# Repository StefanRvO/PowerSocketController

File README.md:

# PowerSocketController
Software for controlling power sockets

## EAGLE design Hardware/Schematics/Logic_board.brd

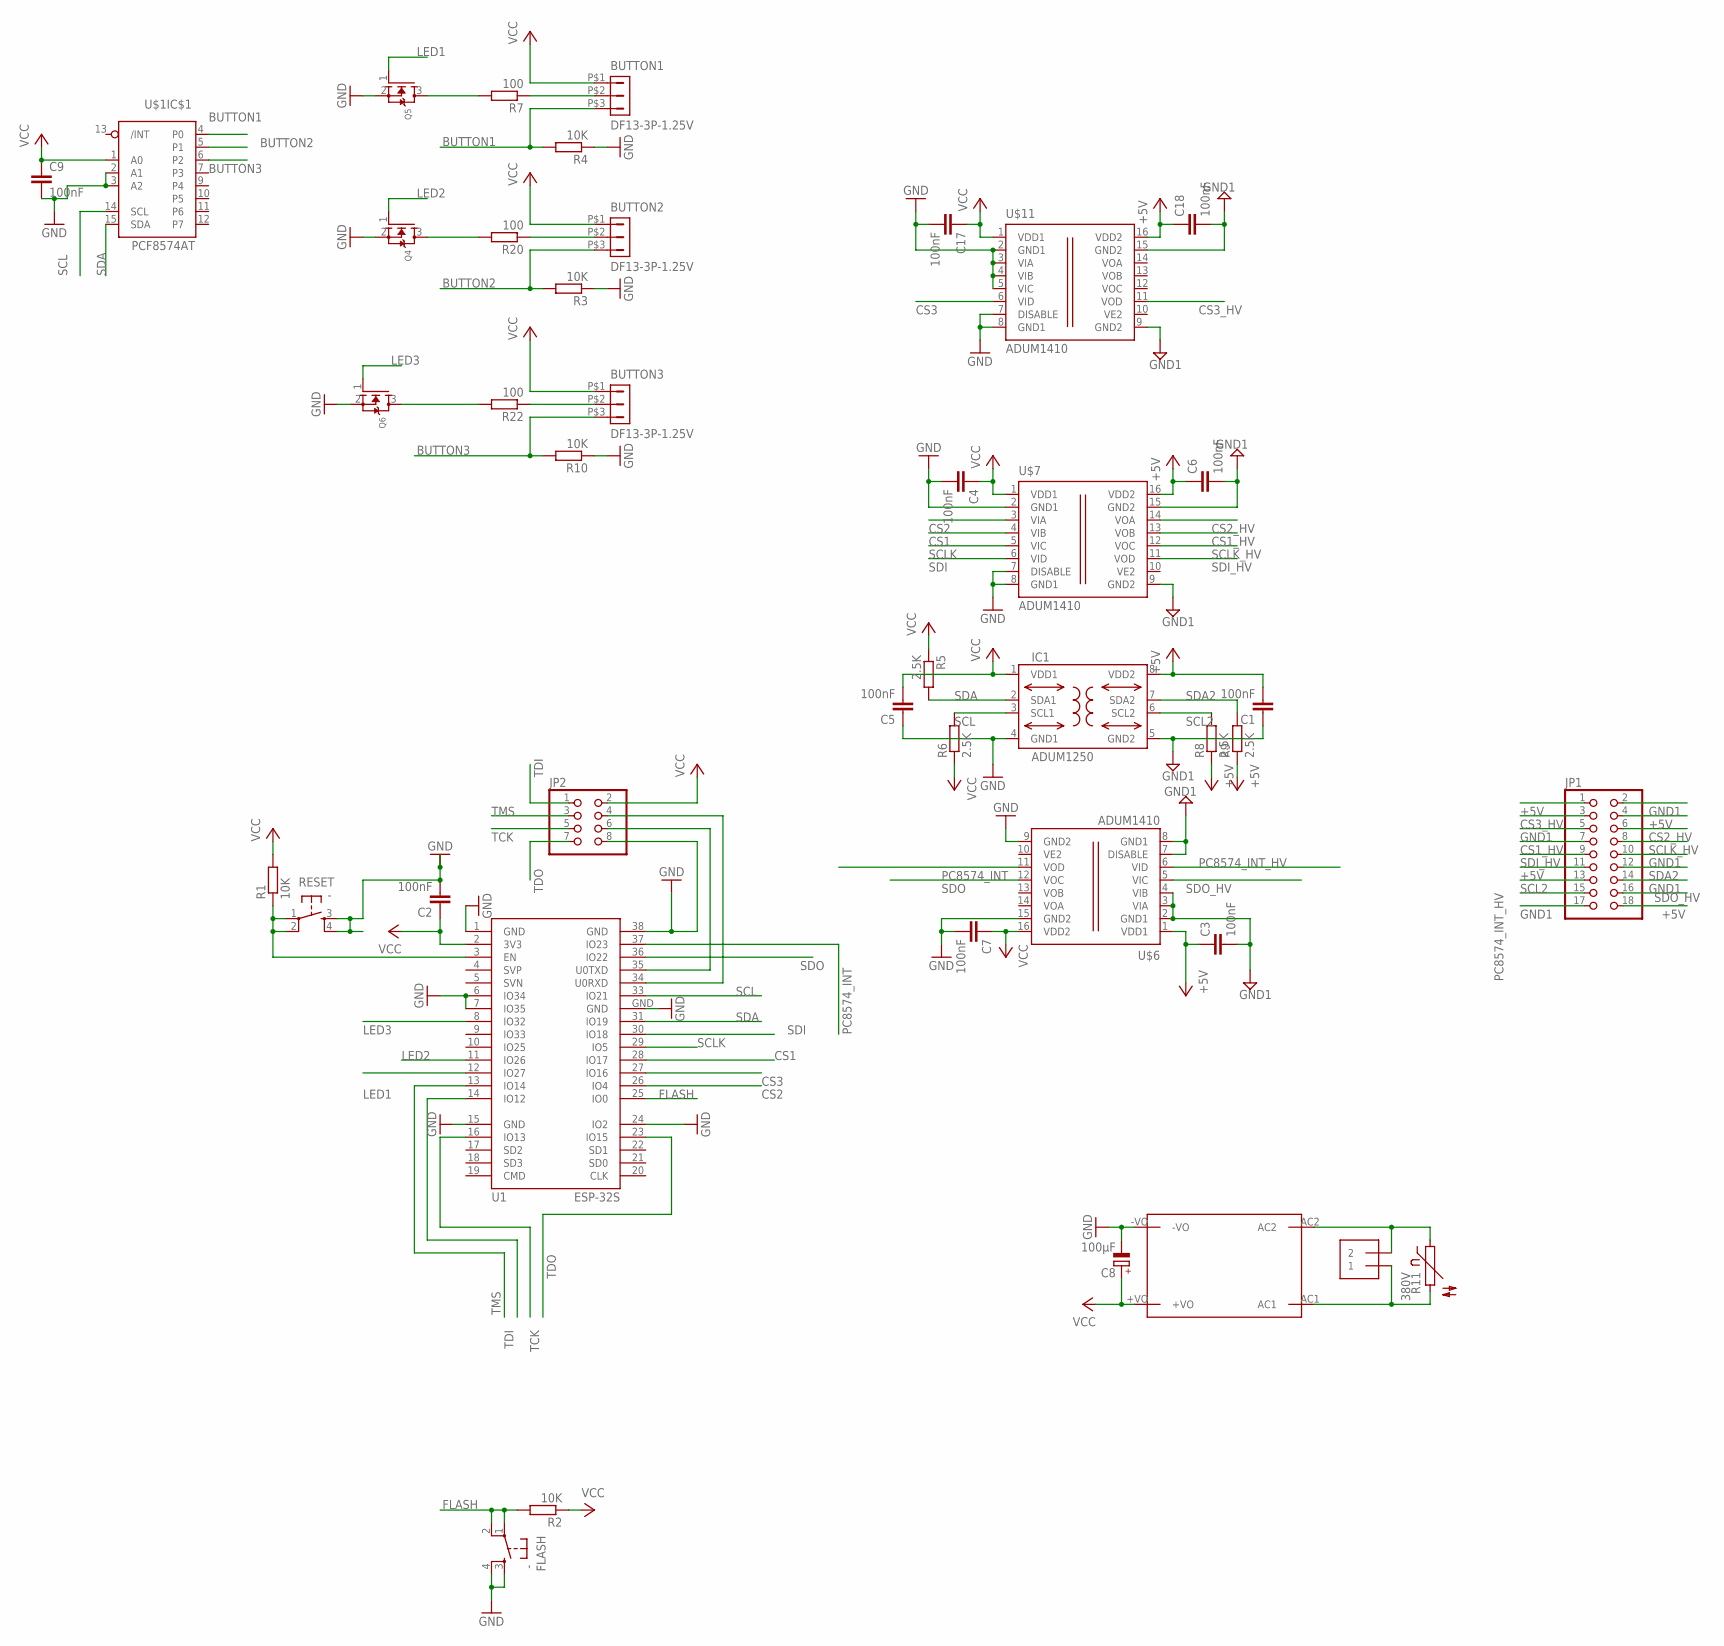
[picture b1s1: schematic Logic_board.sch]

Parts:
BUTTON1, BUTTON2, BUTTON3: DF13-3P-1.25V; DF13C-3P-1.25V
C1, C2, C3, C4, C5, C6, C7, C9, C17, C18: 100nF; C0805
C8: 100µF; E2,5-6
FLASH: -; DTSM-6
IC1: ADUM1250; SO8-COOL
J1: 1X2-3.5MM
JP1: PINHD-2X9; 2X09
JP2: PINHD-2X4; 2X04
Q4, Q5, Q6: MOSFET-NREFLOW; SOT23
R1, R2, R3, R4, R10: 10K; R0805
R5, R6, R8, R9: 2.5K; R0805
R7, R20, R22: 100; R0805
R11: 380V; S14K11
RESET: -; DTSM-6
SUPPLY: 5V; HLK-PM03
U1: ESP-32S
U$1: PCF8574AT; SO16
U$6, U$7, U$11: ADUM1410; SOIC-16

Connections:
+5V: C1.2, C3.1, C6.1, C18.1, IC1.8 (VDD2), JP1.1, JP1.4, JP1.11, JP1.18, R8.1, R9.1, U$6.1 (VDD1), U$7.16 (VDD2), U$11.16 (VDD2)
AC1: J1.1, R11.2, SUPPLY.AC1
AC2: J1.2, R11.1, SUPPLY.AC2
BUTTON1: BUTTON1.P$3 (3), R4.2, U$1.4 (P0)
BUTTON2: BUTTON2.P$3 (3), R3.2, U$1.5 (P1)
BUTTON3: BUTTON3.P$3 (3), R10.2, U$1.6 (P2)
CS1: U1.28 (IO17), U$7.4 (VIB)
CS1_HV: JP1.7, U$7.13 (VOB)
CS2: U1.26 (IO4), U$7.3 (VIA)
CS2_HV: JP1.6, U$7.14 (VOA)
CS3: U1.27 (IO16), U$11.6 (VID)
CS3_HV: JP1.3, U$11.11 (VOD)
FLASH: FLASH.1, FLASH.2, R2.2, U1.25 (IO0)
GND: C2.2, C4.2, C5.1, C7.2, C8.-, C9.2, C17.2, FLASH.3, FLASH.4, IC1.4 (GND1), JP2.8, Q4.2 (S), Q5.2 (S), Q6.2 (S), R3.1, R4.1, R10.1, RESET.3, RESET.4, SUPPLY.-VO, U1.1 (GND), U1.6 (IO34), U1.7 (IO35), U1.15 (GND), U1.24 (IO2), U1.38 (GND), U1.GND, U$1.2 (A1), U$1.3 (A2), U$1.8 (GND), U$6.9 (GND2), U$6.15 (GND2), U$7.2 (GND1), U$7.7 (DISABLE), U$7.8 (GND1), U$11.2 (GND1), U$11.3 (VIA), U$11.4 (VIB), U$11.5 (VIC), U$11.7 (DISABLE), U$11.8 (GND1)
GND1: C1.1, C3.2, C6.2, C18.2, IC1.5 (GND2), JP1.2, JP1.5, JP1.10, JP1.14, JP1.17, U$6.2 (GND1), U$6.3 (VIA), U$6.4 (VIB), U$6.7 (DISABLE), U$6.8 (GND1), U$7.9 (GND2), U$7.15 (GND2), U$11.9 (GND2), U$11.15 (GND2)
LED1: Q5.1 (G), U1.12 (IO27)
LED1_SWITCHED: Q5.3 (D), R7.2
LED2: Q4.1 (G), U1.11 (IO26)
LED2_SWITCHED: Q4.3 (D), R20.2
LED3: Q6.1 (G), U1.8 (IO32)
LED3_SWITCHED: Q6.3 (D), R22.2
unnamed: BUTTON2.P$2 (2), R20.1
unnamed: BUTTON1.P$2 (2), R7.1
unnamed: BUTTON3.P$2 (2), R22.1
unnamed: R1.1, RESET.1, RESET.2, U1.3 (EN)
PC8574_INT: U1.37 (IO23), U$6.11 (VOD)
PC8574_INT_HV: JP1.15, U$6.6 (VID)
RX: JP2.4, U1.34 (U0RXD)
SCL: IC1.3 (SCL1), R6.2, U1.33 (IO21), U$1.14 (SCL)
SCL2: IC1.6 (SCL2), JP1.13, R8.2
SCLK: U1.29 (IO5), U$7.5 (VIC)
SCLK_HV: JP1.8, U$7.12 (VOC)
SDA: IC1.2 (SDA1), R5.2, U1.31 (IO19), U$1.15 (SDA)
SDA2: IC1.7 (SDA2), JP1.12, R9.2
SDI: U1.30 (IO18), U$7.6 (VID)
SDI_HV: JP1.9, U$7.11 (VOD)
SDO: U1.36 (IO22), U$6.12 (VOC)
SDO_HV: JP1.16, U$6.5 (VIC)
TCK: JP2.5, U1.16 (IO13)
TDI: JP2.1, U1.14 (IO12)
TDO: JP2.7, U1.23 (IO15)
TMS: JP2.3, U1.13 (IO14)
TX: JP2.6, U1.35 (U0TXD)
VCC: BUTTON1.P$1 (1), BUTTON2.P$1 (1), BUTTON3.P$1 (1), C2.1, C4.1, C5.2, C7.1, C8.+, C9.1, C17.1, IC1.1 (VDD1), JP2.2, R1.2, R2.1, R5.1, R6.1, SUPPLY.+VO, U1.2 (3V3), U$1.1 (A0), U$1.16 (VCC), U$6.16 (VDD2), U$7.1 (VDD1), U$11.1 (VDD1)

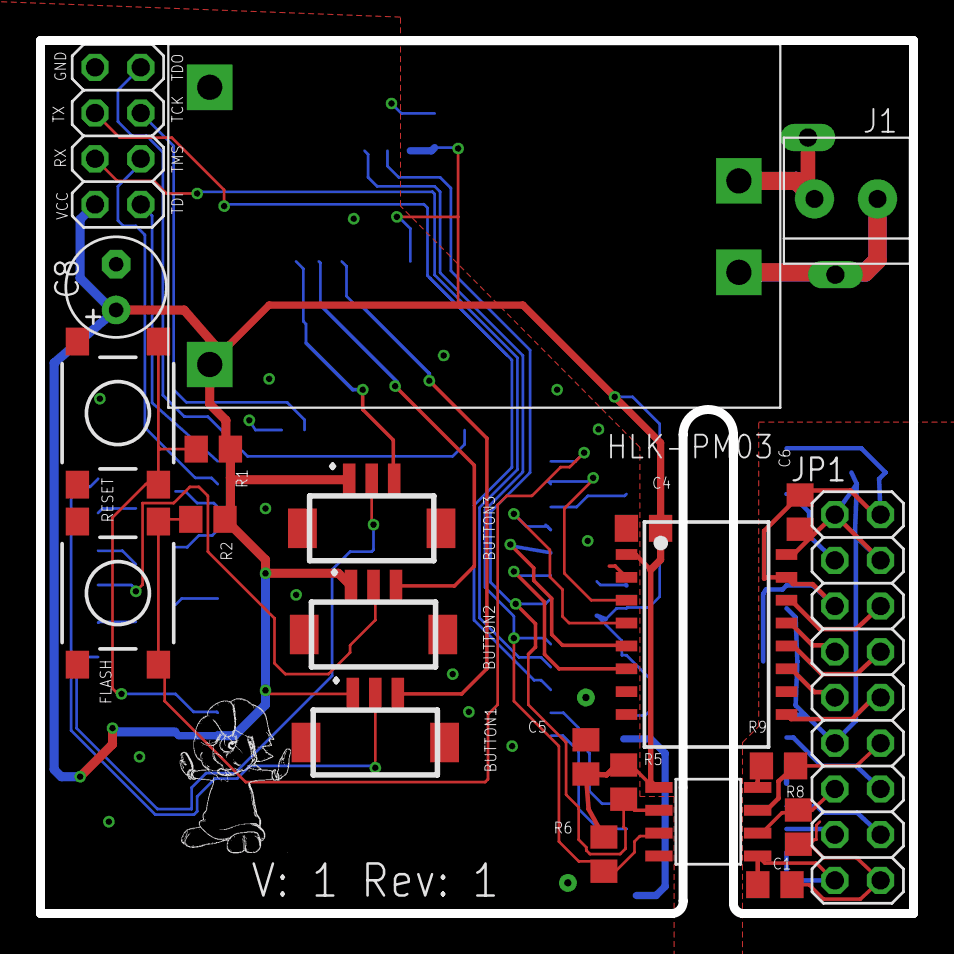
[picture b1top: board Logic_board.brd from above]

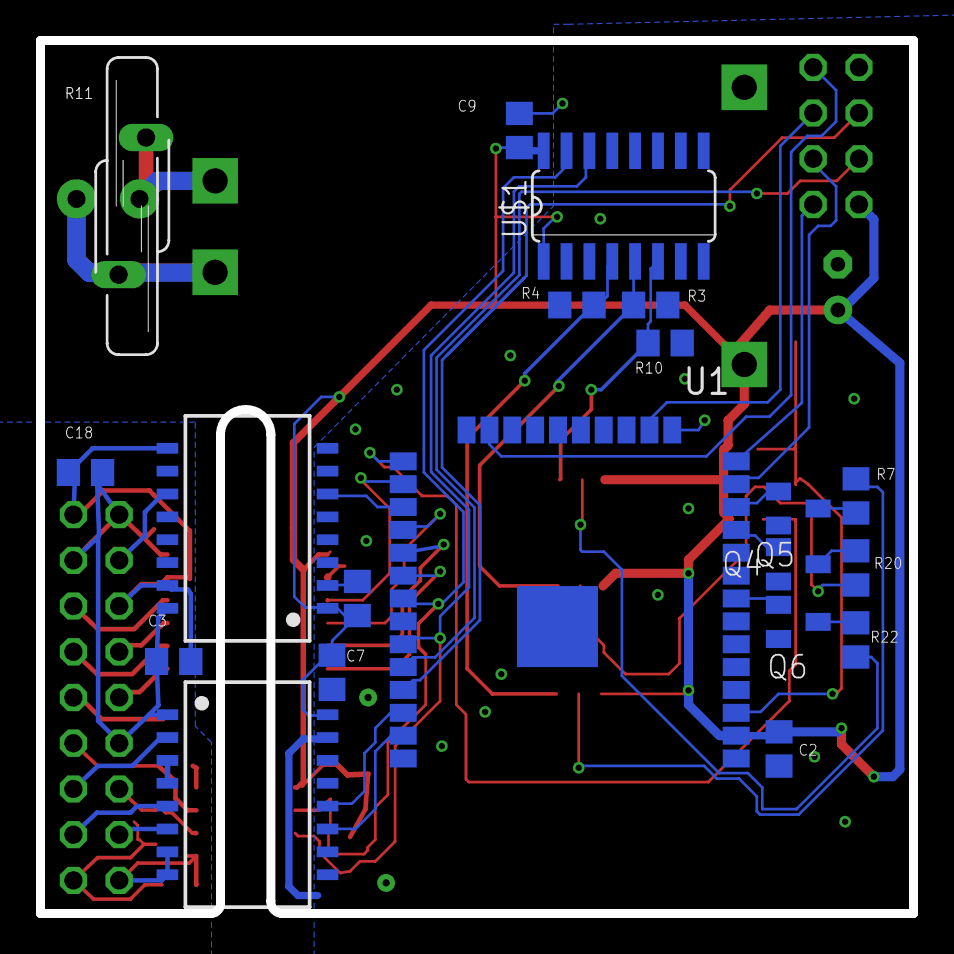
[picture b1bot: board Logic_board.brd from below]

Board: 2 copper layers, 48.5 x 48.5 mm, 42 parts (20 on the bottom side), 44 nets.

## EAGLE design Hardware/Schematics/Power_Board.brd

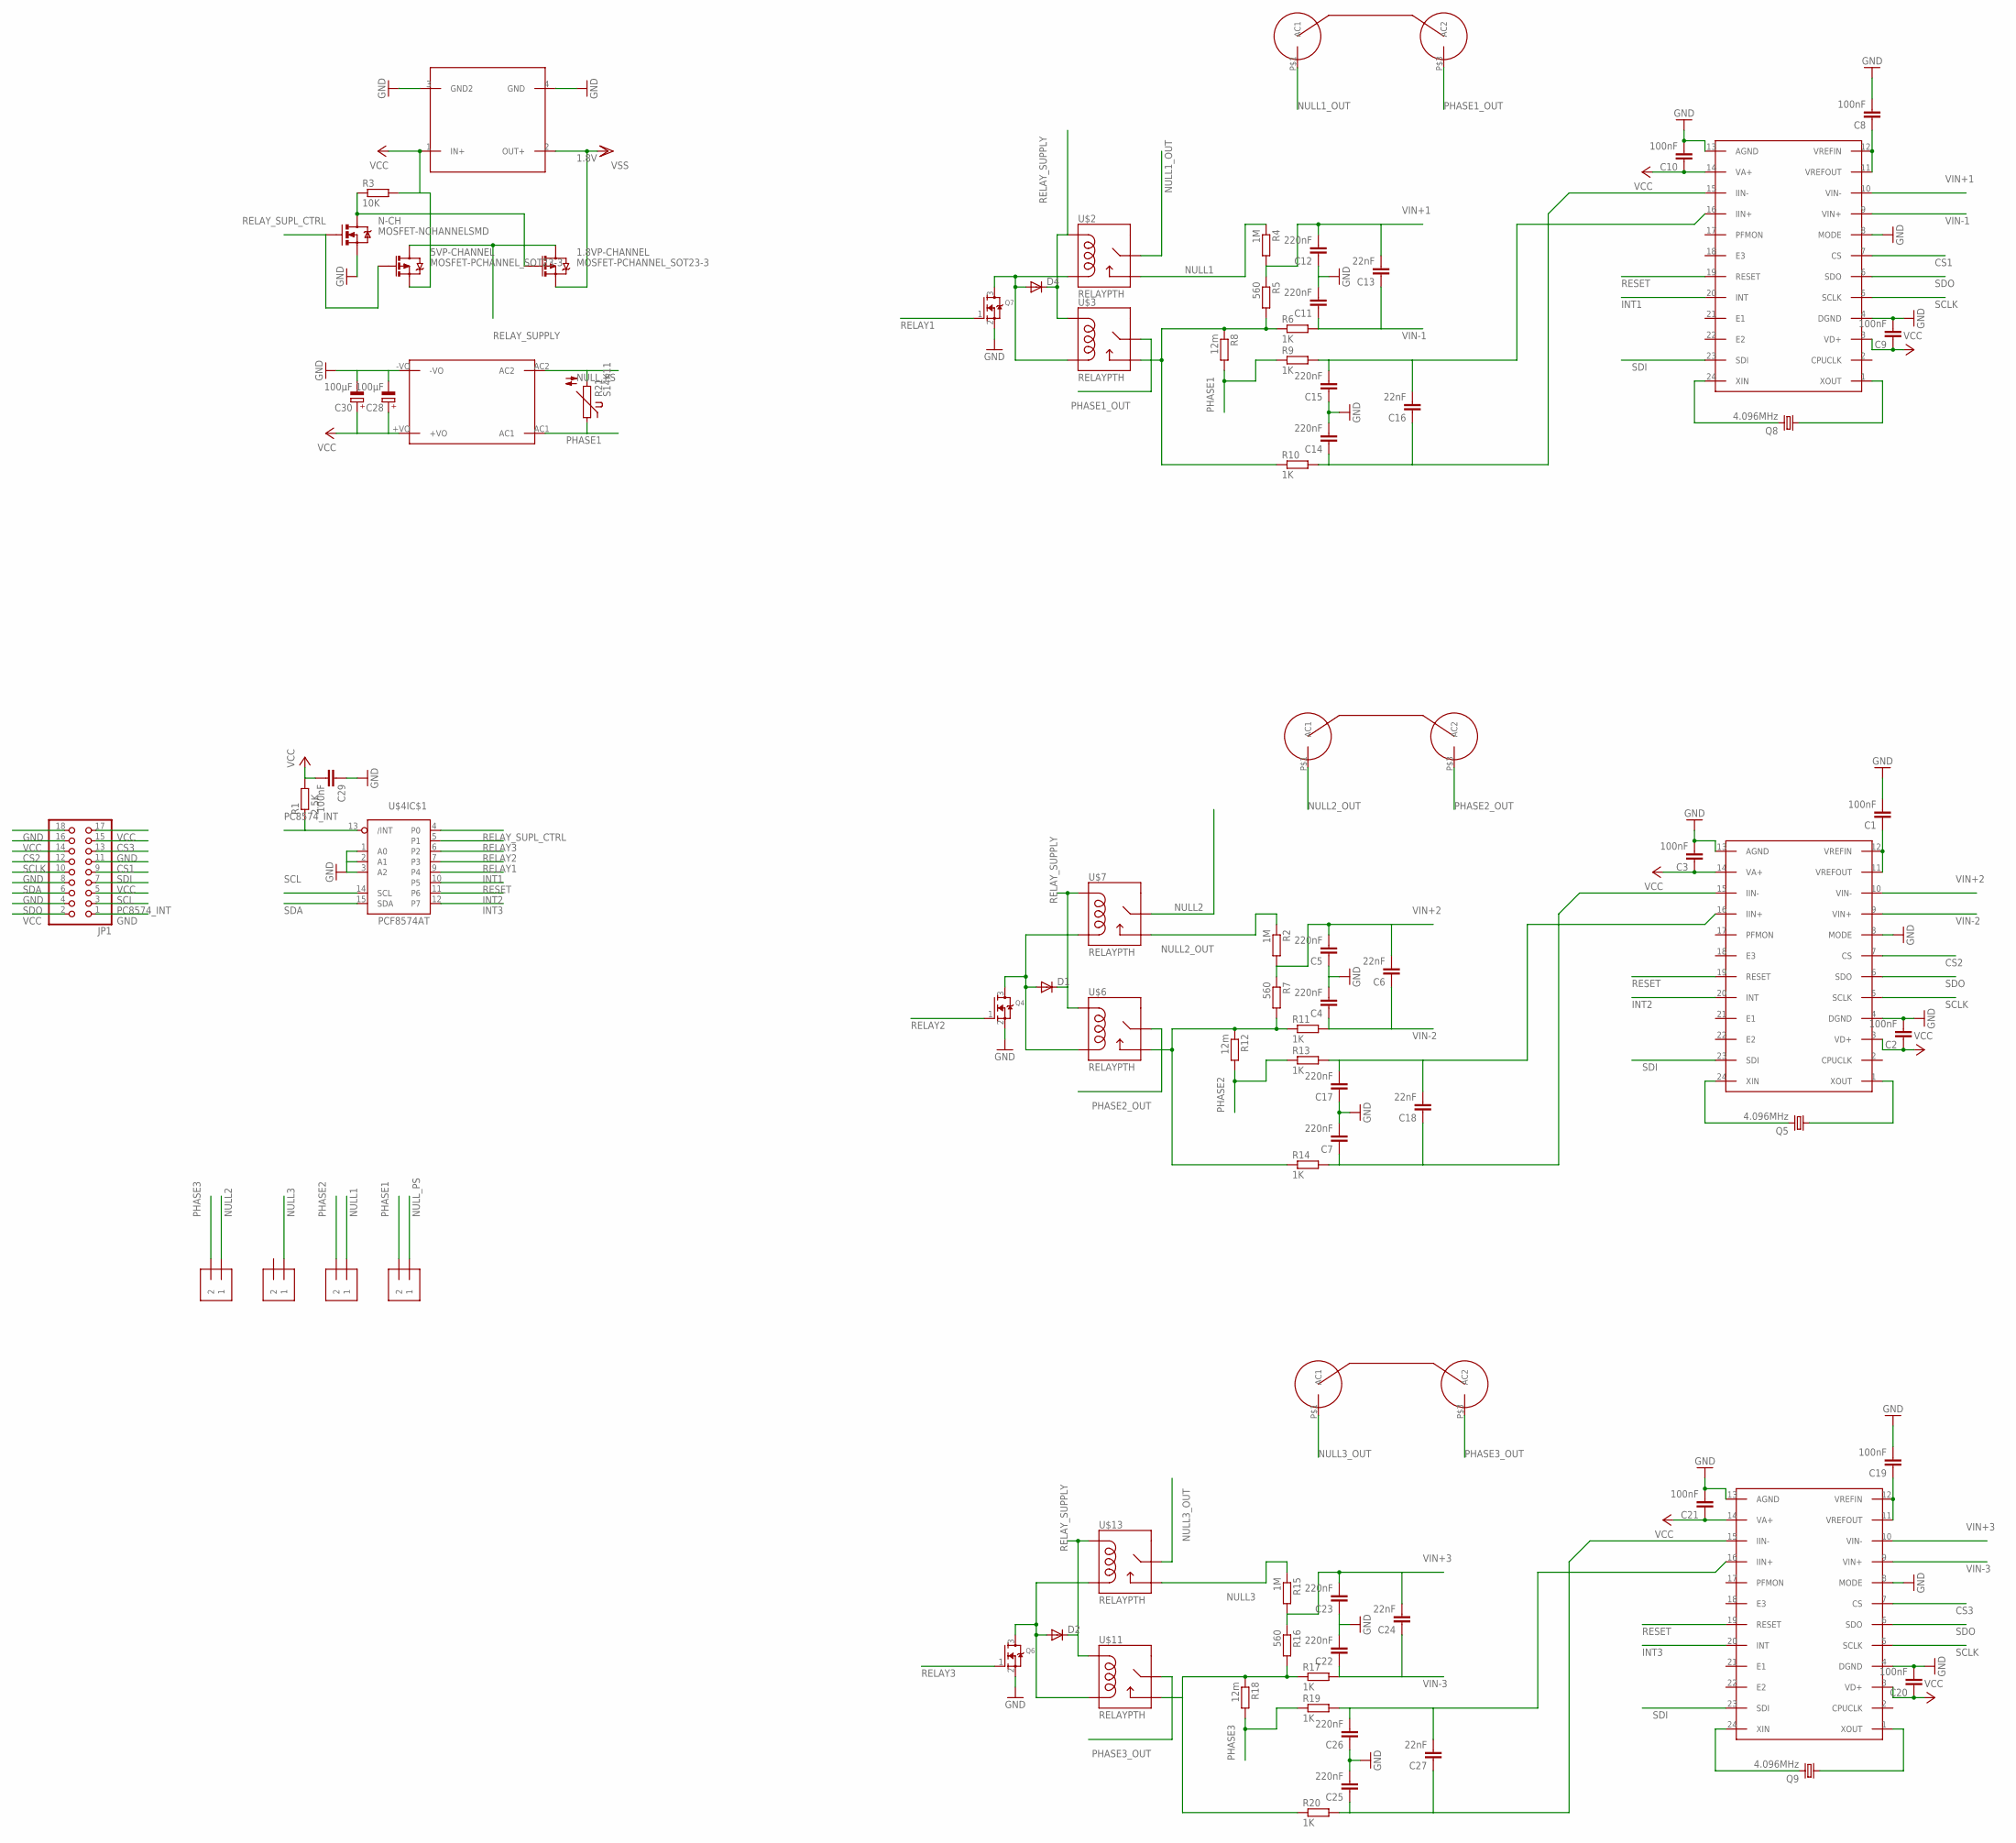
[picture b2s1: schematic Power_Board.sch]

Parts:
1.8VP-CHANNEL, 5VP-CHANNEL: MOSFET-PCHANNEL_SOT23-3; SOT23-3
C1, C2, C3, C8, C9, C10, C19, C20, C21, C29: 100nF; C0805
C4, C5, C7, C11, C12, C14, C15, C17, C22, C23, C25, C26: 220nF; C0805
C6, C13, C16, C18, C24, C27: 22nF; C0805
C28, C30: 100µF; E5-6
D1, D2, D4: DIODE-DO-214AC; DO-214AC
J1, J2, J3, J4: 1X2-3.5MM
JP1: PINHD-2X9; 2X09
N-CH: MOSFET-NCHANNELSMD; SOT23-3
Q4, Q6, Q7: MOSFET-NREFLOW; SOT23
Q5, Q8, Q9: 4.096MHz; HC49U70
R1: 2.5K; R0805
R2, R4, R15: 1M; R0805
R3: 10K; R0805
R5, R7, R16: 560; R1206
R6, R9, R10, R11, R13, R14, R17, R19, R20: 1K; R0805
R8, R12, R18: 12m; R2512
R21: S14K11
U$1: STEP_DOWN
U$2, U$3, U$6, U$7, U$11, U$13: RELAYPTH; SRD-05VDC-SL-C
U$4: PCF8574AT; SO16
U$5: HLK-PM03
U$8, U$9, U$14: CS5463; SSOP24
U$10, U$12, U$15: POWER_SOCKET_EU; POWER_SOCKET_EU_PLATED_THROUGH

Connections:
1.8V: 1.8VP-CHANNEL.2 (S), U$1.2 (OUT+)
CS1: JP1.11, U$9.7 (CS)
CS2: JP1.14, U$8.7 (CS)
CS3: JP1.15, U$14.7 (CS)
GND: C1.2, C2.2, C3.2, C4.2, C5.1, C7.2, C8.2, C9.2, C10.2, C11.2, C12.1, C14.2, C15.1, C17.1, C19.2, C20.2, C21.2, C22.2, C23.1, C25.2, C26.1, C28.-, C29.1, C30.-, JP1.1, JP1.6, JP1.10, JP1.13, JP1.18, N-CH.2 (S), Q4.2 (S), Q6.2 (S), Q7.2 (S), U$1.3 (GND2), U$1.4 (GND), U$4.1 (A0), U$4.2 (A1), U$4.3 (A2), U$4.8 (GND), U$5.-VO, U$8.4 (DGND), U$8.8 (MODE), U$8.13 (AGND), U$9.4 (DGND), U$9.8 (MODE), U$9.13 (AGND), U$14.4 (DGND), U$14.8 (MODE), U$14.13 (AGND)
INT1: U$4.9 (P4), U$9.20 (INT)
INT2: U$4.11 (P6), U$8.20 (INT)
INT3: U$4.12 (P7), U$14.20 (INT)
unnamed: D1.A, Q4.3 (D), U$6.COIL0, U$7.COIL0
unnamed: Q5.1, U$8.1 (XOUT)
unnamed: C1.1, U$8.11 (VREFOUT), U$8.12 (VREFIN)
unnamed: C7.1, C18.1, R14.2, U$8.15 (IIN-)
unnamed: Q5.2, U$8.24 (XIN)
unnamed: R7.2, R11.1, R12.1, R14.1, U$6.SWOPEN
unnamed: C17.2, C18.2, R13.2, U$8.16 (IIN+)
unnamed: D2.A, Q6.3 (D), U$11.COIL0, U$13.COIL0
unnamed: Q9.1, U$14.1 (XOUT)
unnamed: 1.8VP-CHANNEL.1 (G), N-CH.3 (D), R3.1
unnamed: C19.1, U$14.11 (VREFOUT), U$14.12 (VREFIN)
unnamed: D4.A, Q7.3 (D), U$2.COIL0, U$3.COIL0
unnamed: C25.1, C27.1, R20.2, U$14.15 (IIN-)
unnamed: Q9.2, U$14.24 (XIN)
unnamed: Q8.1, U$9.1 (XOUT)
unnamed: R16.2, R17.1, R18.1, R20.1, U$11.SWOPEN
unnamed: C26.2, C27.2, R19.2, U$14.16 (IIN+)
unnamed: R5.2, R6.1, R8.1, R10.1, U$3.SWOPEN
unnamed: C15.2, C16.2, R9.2, U$9.16 (IIN+)
unnamed: C8.1, U$9.11 (VREFOUT), U$9.12 (VREFIN)
unnamed: C14.1, C16.1, R10.2, U$9.15 (IIN-)
unnamed: Q8.2, U$9.24 (XIN)
NULL1: J2.1, R4.1, U$2.SWOPEN
NULL1_OUT: U$2.SWCOMMON, U$12.P$1 (AC1)
NULL2: J1.1, R2.1, U$7.SWOPEN
NULL2_OUT: U$7.SWCOMMON, U$10.P$1 (AC1)
NULL3: J3.1, R15.1, U$13.SWOPEN
NULL3_OUT: U$13.SWCOMMON, U$15.P$1 (AC1)
NULL_PS: J4.1, R21.2, U$5.AC2
PC8574_INT: JP1.3, R1.1, U$4.13 (/INT)
PHASE1: J4.2, R8.2, R9.1, R21.1, U$5.AC1
PHASE1_OUT: U$3.SWCOMMON, U$12.P$3 (AC2)
PHASE2: J2.2, R12.2, R13.1
PHASE2_OUT: U$6.SWCOMMON, U$10.P$3 (AC2)
PHASE3: J1.2, R18.2, R19.1
PHASE3_OUT: U$11.SWCOMMON, U$15.P$3 (AC2)
RELAY1: Q7.1 (G), U$4.7 (P3)
RELAY2: Q4.1 (G), U$4.6 (P2)
RELAY3: Q6.1 (G), U$4.5 (P1)
RELAY_SUPL_CTRL: 5VP-CHANNEL.1 (G), N-CH.1 (G), U$4.4 (P0)
RELAY_SUPPLY: 1.8VP-CHANNEL.3 (D), 5VP-CHANNEL.3 (D), D1.C, D2.C, D4.C, U$2.COIL1, U$3.COIL1, U$6.COIL1, U$7.COIL1, U$11.COIL1, U$13.COIL1
RESET: U$4.10 (P5), U$8.19 (RESET), U$9.19 (RESET), U$14.19 (RESET)
SCL: JP1.5, U$4.14 (SCL)
SCLK: JP1.12, U$8.5 (SCLK), U$9.5 (SCLK), U$14.5 (SCLK)
SDA: JP1.8, U$4.15 (SDA)
SDI: JP1.9, U$8.23 (SDI), U$9.23 (SDI), U$14.23 (SDI)
SDO: JP1.4, U$8.6 (SDO), U$9.6 (SDO), U$14.6 (SDO)
VCC: 5VP-CHANNEL.2 (S), C2.1, C3.1, C9.1, C10.1, C20.1, C21.1, C28.+, C29.2, C30.+, JP1.2, JP1.7, JP1.16, JP1.17, R1.2, R3.2, U$1.1 (IN+), U$4.16 (VCC), U$5.+VO, U$8.3 (VD+), U$8.14 (VA+), U$9.3 (VD+), U$9.14 (VA+), U$14.3 (VD+), U$14.14 (VA+)
VIN+1: C12.2, C13.2, R4.2, R5.1, U$9.10 (VIN-)
VIN+2: C5.2, C6.2, R2.2, R7.1, U$8.10 (VIN-)
VIN+3: C23.2, C24.2, R15.2, R16.1, U$14.10 (VIN-)
VIN-1: C11.1, C13.1, R6.2, U$9.9 (VIN+)
VIN-2: C4.1, C6.1, R11.2, U$8.9 (VIN+)
VIN-3: C22.1, C24.1, R17.2, U$14.9 (VIN+)

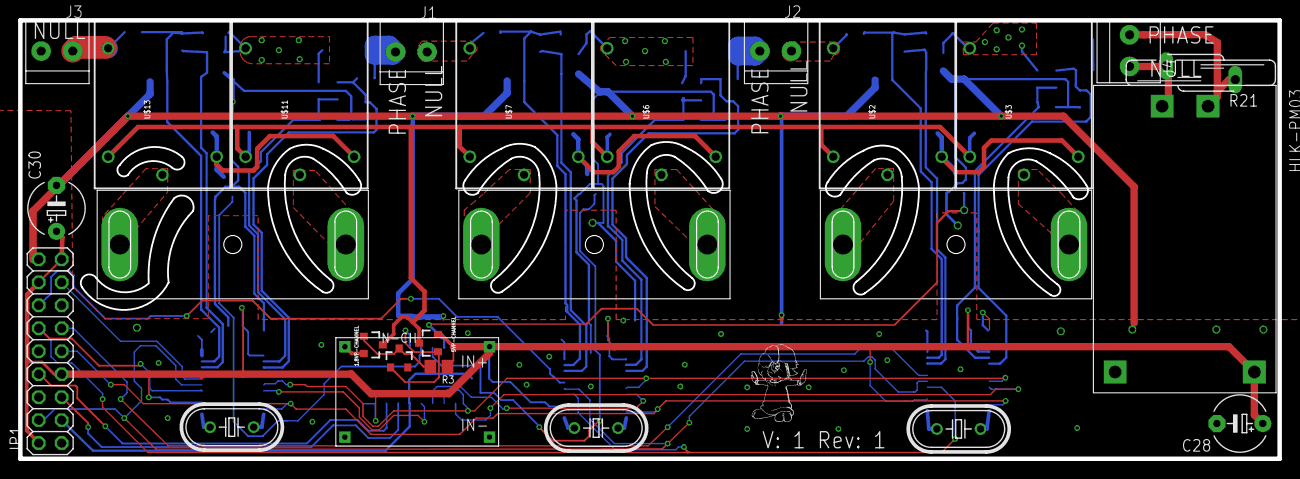
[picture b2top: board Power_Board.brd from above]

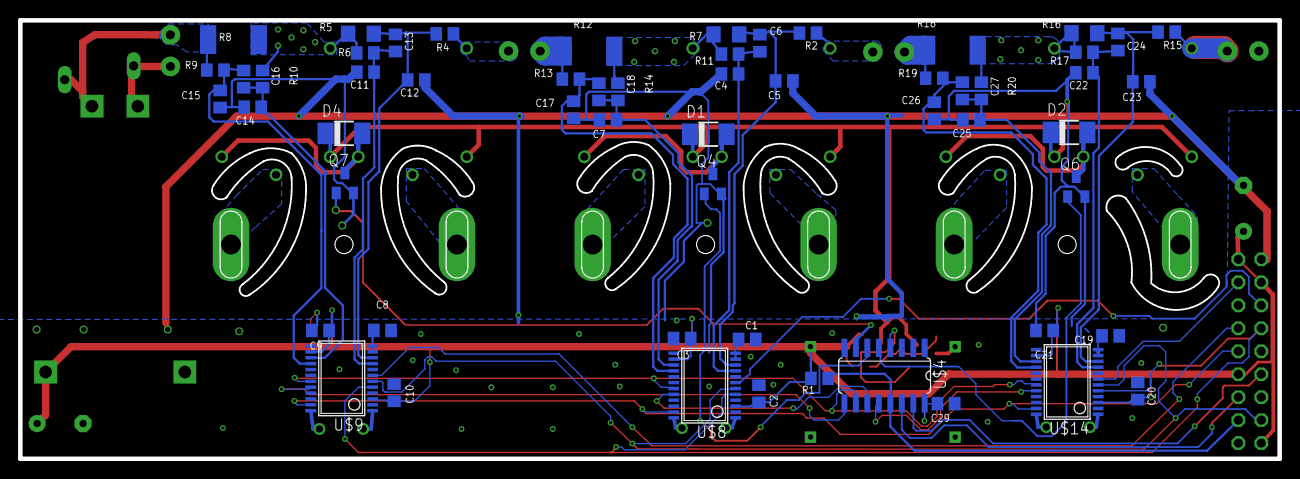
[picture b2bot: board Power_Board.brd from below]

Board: 2 copper layers, 139.3 x 48.5 mm, 83 parts (57 on the bottom side), 62 nets.

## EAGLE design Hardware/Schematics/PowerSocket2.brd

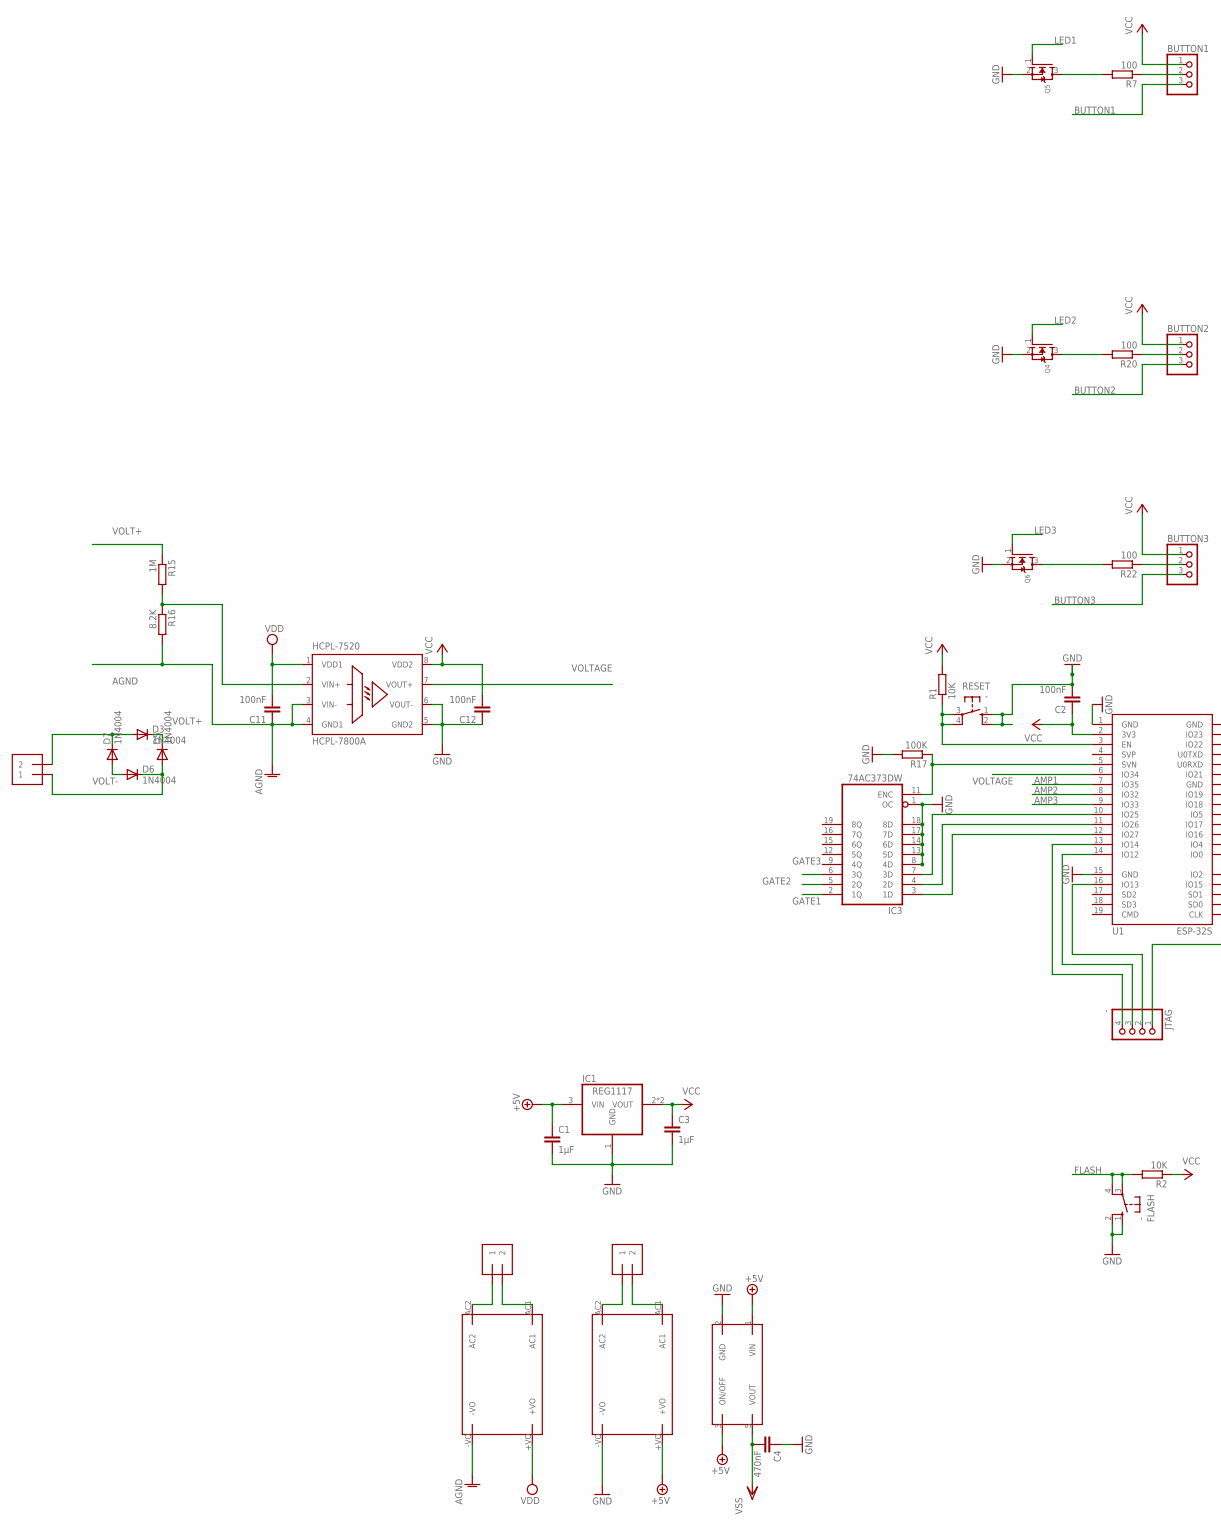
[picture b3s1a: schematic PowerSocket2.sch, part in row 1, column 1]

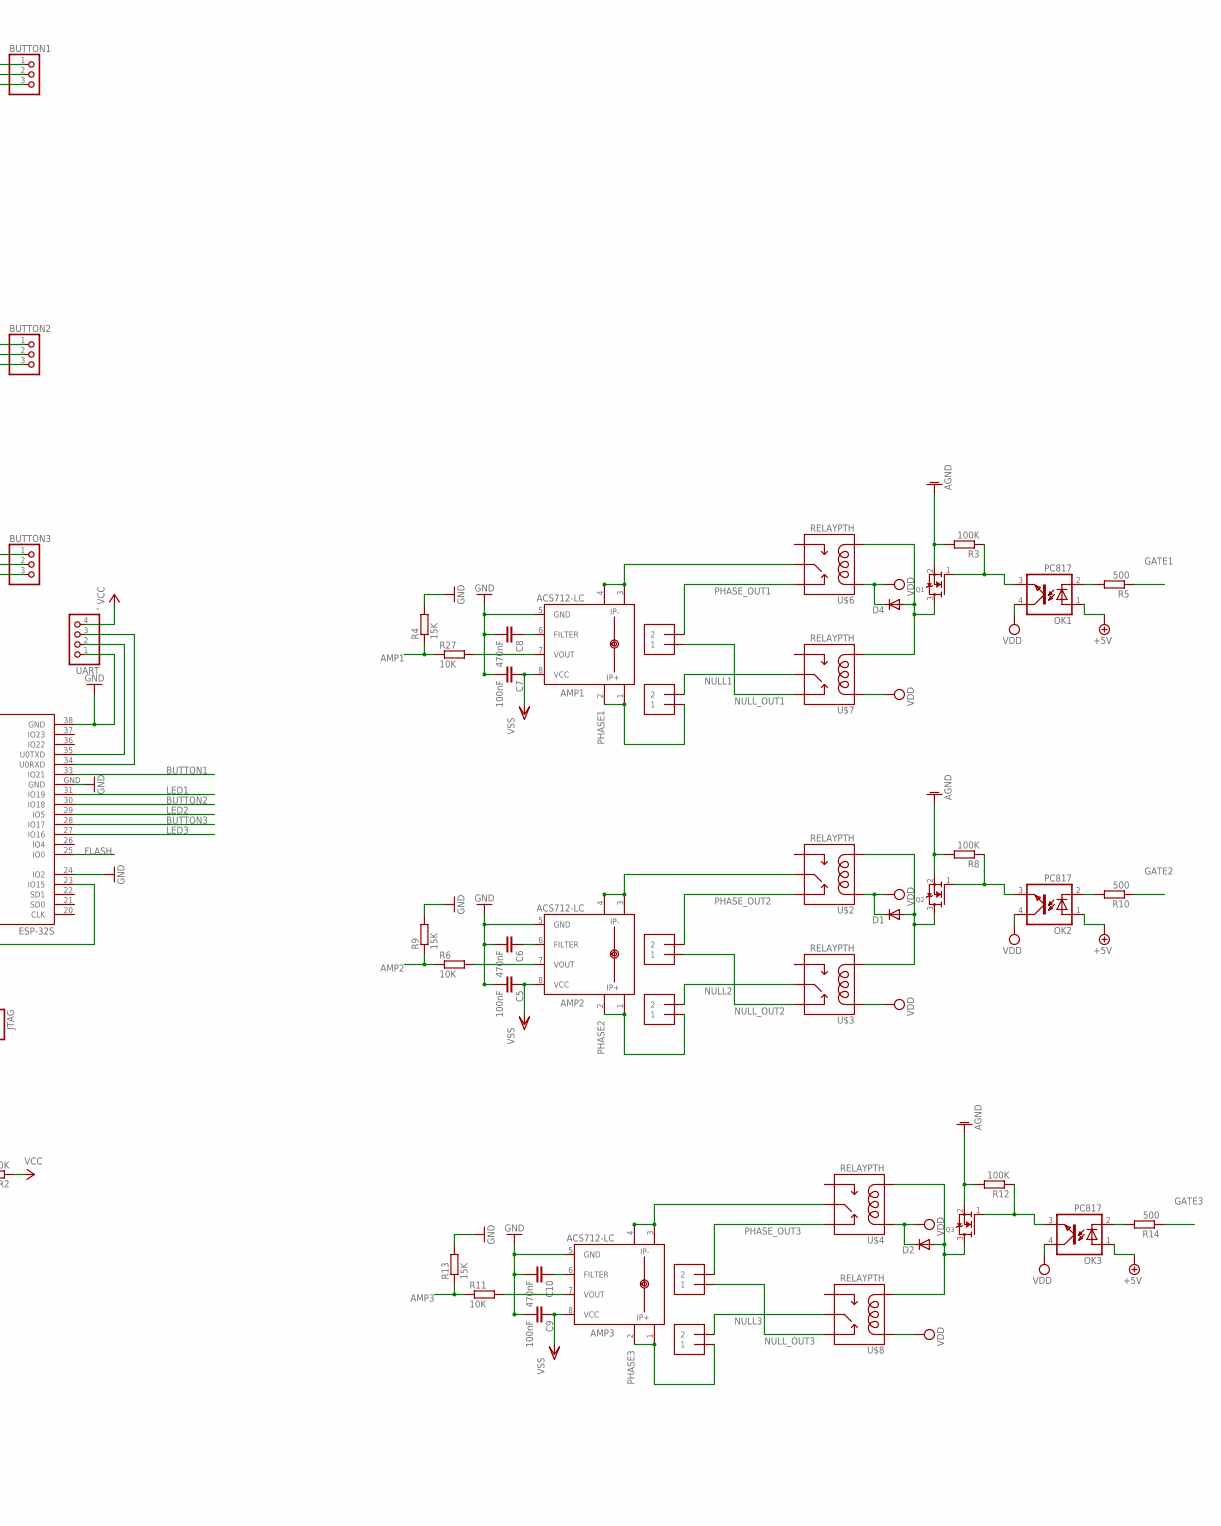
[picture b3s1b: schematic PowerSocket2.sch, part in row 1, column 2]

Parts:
4.5V_REG: S1112; SOT23-5
AMP1, AMP2, AMP3: ACS712-LC; SOIC8
BUTTON1, BUTTON2, BUTTON3: PINHD-1X3; 1X03
C1, C3: 1µF; C025-024X044
C2, C11, C12: 100nF; C1206
C4, C6, C8, C10: 470nF; C0805
C5, C7, C9: 100nF; C0805
D1, D2, D4: DIODE-DO-214AC; DO-214AC
D3, D5, D6, D7: 1N4004; DO41-10
FLASH: -; B3F-10XX
HCPL-7520: HCPL-7800A; DIP8
IC1: REG1117; SOT223
IC3: 74AC373DW; SO20W
J1, J2, J3, J4, J5, J6, J7, J8, J9: 1X2-3.5MM
JTAG: -; 1X04
OK1, OK2, OK3: PC817; DIL04
Q1, Q2, Q3, Q4, Q5, Q6: MOSFET-NREFLOW; SOT23
R1, R2, R6, R11, R27: 10K; R0805
R3, R8, R12, R17: 100K; R0805
R4, R9, R13: 15K; R0805
R5, R10, R14: 500; R0805
R7, R20, R22: 100; R0805
R15: 1M; 0207/10
R16: 8.2K; 0207/10
RESET: -; B3F-10XX
U1: ESP-32S
U$1, U$5: HLK-PM03
U$2, U$3, U$4, U$6, U$7, U$8: RELAYPTH; SRD-05VDC-SL-C
UART: -; 1X04

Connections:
+5V: 4.5V_REG.1 (VIN), 4.5V_REG.3 (ON/OFF), C1.1, IC1.3 (VIN), OK1.1 (A), OK2.1 (A), OK3.1 (A), U$1.+VO
AGND: C11.1, HCPL-7520.3 (VIN-), HCPL-7520.4 (GND1), Q1.2 (S), Q2.2 (S), Q3.2 (S), R3.2, R8.2, R12.2, R16.2, U$5.-VO
AMP1: R4.1, R27.1, U1.7 (IO35)
AMP2: R6.1, R9.1, U1.8 (IO32)
AMP3: R11.1, R13.1, U1.9 (IO33)
BUTTON1: BUTTON1.3, U1.33 (IO21)
BUTTON2: BUTTON2.3, U1.30 (IO18)
BUTTON3: BUTTON3.3, U1.28 (IO17)
FLASH: FLASH.3, FLASH.4 (P1), R2.2, U1.25 (IO0)
GATE: OK1.3 (EMIT), Q1.1 (G), R3.1
GATE1: IC3.2 (1Q), R5.1
GATE2: IC3.5 (2Q), R10.1
GATE3: IC3.6 (3Q), R14.1
GATE4: OK2.3 (EMIT), Q2.1 (G), R8.1
GATE5: OK3.3 (EMIT), Q3.1 (G), R12.1
GND: 4.5V_REG.2 (GND), AMP1.5 (GND), AMP2.5 (GND), AMP3.5 (GND), C1.2, C2.2, C3.2, C4.1, C5.2, C6.2, C7.2, C8.2, C9.2, C10.2, C12.1, FLASH.1 (S), FLASH.2 (S1), HCPL-7520.5 (GND2), HCPL-7520.6 (VOUT-), IC1.1 (GND), IC3.1 (OC), IC3.8 (4D), IC3.10 (GND), IC3.13 (5D), IC3.14 (6D), IC3.17 (7D), IC3.18 (8D), Q4.2 (S), Q5.2 (S), Q6.2 (S), R4.2, R9.2, R13.2, R17.2, RESET.1 (S), RESET.2 (S1), U1.1 (GND), U1.15 (GND), U1.24 (IO2), U1.38 (GND), U1.GND, U$1.-VO, UART.1
LED1: Q5.1 (G), U1.31 (IO19)
LED1_SWITCHED: Q5.3 (D), R7.2
LED2: Q4.1 (G), U1.29 (IO5)
LED2_SWITCHED: Q4.3 (D), R20.2
LED3: Q6.1 (G), U1.27 (IO16)
LED3_SWITCHED: Q6.3 (D), R22.2
unnamed: D4.A, Q1.3 (D), U$6.COIL0, U$7.COIL0
unnamed: JTAG.1, U1.23 (IO15)
unnamed: JTAG.2, U1.16 (IO13)
unnamed: JTAG.3, U1.14 (IO12)
unnamed: JTAG.4, U1.13 (IO14)
unnamed: J4.2, U$5.AC1
unnamed: BUTTON2.2, R20.1
unnamed: J4.1, U$5.AC2
unnamed: BUTTON1.2, R7.1
unnamed: OK1.2 (C), R5.2
unnamed: BUTTON3.2, R22.1
unnamed: AMP2.6 (FILTER), C6.1
unnamed: AMP2.7 (VOUT), R6.2
unnamed: D1.A, Q2.3 (D), U$2.COIL0, U$3.COIL0
unnamed: OK2.2 (C), R10.2
unnamed: AMP2.3 (IP-), AMP2.4 (IP-1), U$2.SWCOMMON
unnamed: AMP1.6 (FILTER), C8.1
unnamed: AMP1.3 (IP-), AMP1.4 (IP-1), U$6.SWCOMMON
unnamed: AMP3.6 (FILTER), C10.1
unnamed: AMP3.7 (VOUT), R11.2
unnamed: D2.A, Q3.3 (D), U$4.COIL0, U$8.COIL0
unnamed: OK3.2 (C), R14.2
unnamed: AMP3.3 (IP-), AMP3.4 (IP-1), U$4.SWCOMMON
unnamed: IC3.11 (ENC), R17.1, U1.5 (SVN)
unnamed: IC3.3 (1D), U1.12 (IO27)
unnamed: IC3.4 (2D), U1.11 (IO26)
unnamed: IC3.7 (3D), U1.10 (IO25)
unnamed: D3.A, D7.C, J9.2
unnamed: D5.A, D6.C, J9.1
unnamed: HCPL-7520.2 (VIN+), R15.2, R16.1
unnamed: AMP1.7 (VOUT), R27.2
unnamed: R1.1, RESET.3, RESET.4 (P1), U1.3 (EN)
unnamed: U1.35 (U0TXD), UART.2
unnamed: U1.34 (U0RXD), UART.3
NULL1: J2.2, U$7.SWCOMMON
NULL2: J6.2, U$3.SWCOMMON
NULL3: J8.2, U$8.SWCOMMON
NULL_MIC: J3.1, U$1.AC2
NULL_OUT1: J1.1, U$7.SWCLOSED (SWCLOSE)
NULL_OUT2: J5.1, U$3.SWCLOSED (SWCLOSE)
NULL_OUT3: J7.1, U$8.SWCLOSED (SWCLOSE)
PHASE1: AMP1.1 (IP+), AMP1.2 (IP+1), J2.1
PHASE2: AMP2.1 (IP+), AMP2.2 (IP+1), J6.1
PHASE3: AMP3.1 (IP+), AMP3.2 (IP+1), J8.1
PHASE_MIC: J3.2, U$1.AC1
PHASE_OUT1: J1.2, U$6.SWCLOSED (SWCLOSE)
PHASE_OUT2: J5.2, U$2.SWCLOSED (SWCLOSE)
PHASE_OUT3: J7.2, U$4.SWCLOSED (SWCLOSE)
VCC: BUTTON1.1, BUTTON2.1, BUTTON3.1, C2.1, C3.1, C12.2, HCPL-7520.8 (VDD2), IC1.2 (VOUT), IC1.4 (VOUT), IC3.20 (VCC), R1.2, R2.1, U1.2 (3V3), UART.4
VDD: C11.2, D1.C, D2.C, D4.C, HCPL-7520.1 (VDD1), OK1.4 (COL), OK2.4 (COL), OK3.4 (COL), U$2.COIL1, U$3.COIL1, U$4.COIL1, U$5.+VO, U$6.COIL1, U$7.COIL1, U$8.COIL1
VOLT+: D3.C, D5.C, R15.1
VOLT-: D6.A, D7.A
VOLTAGE: HCPL-7520.7 (VOUT+), U1.6 (IO34)
VSS: 4.5V_REG.5 (VOUT), AMP1.8 (VCC), AMP2.8 (VCC), AMP3.8 (VCC), C4.2, C5.1, C7.1, C9.1

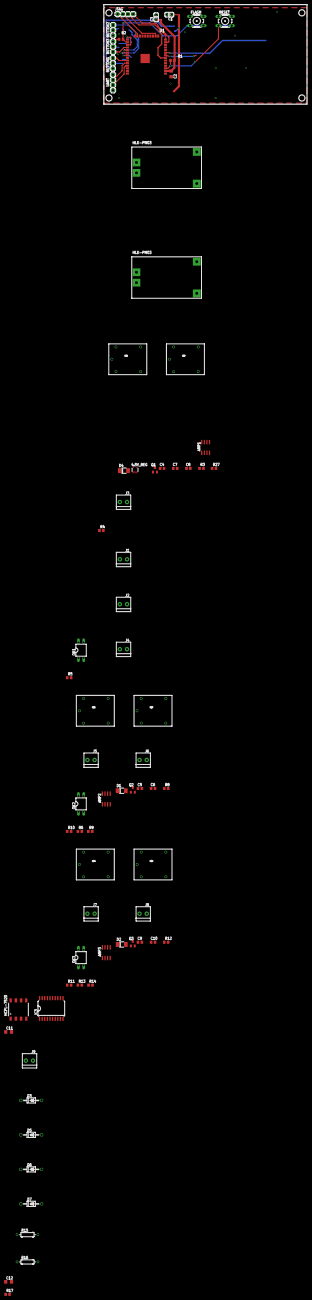
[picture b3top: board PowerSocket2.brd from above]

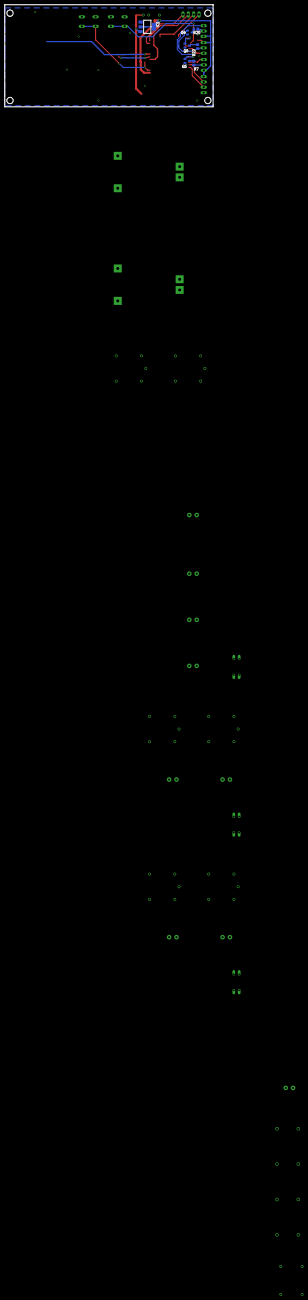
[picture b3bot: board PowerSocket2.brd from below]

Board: 2 copper layers, 99.0 x 48.5 mm, 80 parts (7 on the bottom side), 76 nets.

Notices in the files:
parts and their libraries:
esp32: Creative Commons Attribution-ShareAlike 4.0 International
